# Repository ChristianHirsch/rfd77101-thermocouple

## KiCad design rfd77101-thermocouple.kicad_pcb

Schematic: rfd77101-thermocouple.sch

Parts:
C5: 1u; C_0603_1608Metric
C6: 10n; C_0603_1608Metric
C7: 100n; C_0603_1608Metric
D3: LED; LED_0603_1608Metric
J3: Conn_01x07; PinHeader_1x07_P2.54mm_Vertical
J4: Conn_01x02; TerminalBlock_RND_205-00241_1x02_P10.16mm_Horizontal
R4: R; R_0603_1608Metric
U1: RFD77101; RFDigital_RFD77101
U4: MAX31855KASA; SOIC-8_3.9x4.9mm_P1.27mm

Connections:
/BATT_V: U1.22; also elsewhere on the board
/BATT_V_EN: U1.12; also elsewhere on the board
/GPIO0: J3.6, U1.25
/GPIO1: J3.7, U1.23
/LED_1: D3.2, U1.11
/MISO: U1.27, U4.7
/SCK: U1.29, U4.5
/SWDCLK: J3.5, U1.9
/SWDIO/RESET: J3.4, U1.8
/~SS: U1.28, U4.6
GND: C5.2, C7.2, J3.1, R4.2, U1.1, U1.2, U1.4, U1.6, U1.19, U1.30, U1.42, U1.43, U1.44, U1.45, U4.1; also elsewhere on the board
unnamed: C6.1, J4.2, U4.3
unnamed: C6.2, J4.1, U4.2
unnamed: D3.1, R4.1
VBUS: J3.3; also elsewhere on the board
VDD: C5.1, C7.1, U1.7, U4.4; also elsewhere on the board

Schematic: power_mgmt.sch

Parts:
C1, C2: 4.7u; C_0603_1608Metric
C3, C4: 1u; C_0603_1608Metric
D1, D2: BAT20J; D_SOD-323
J1: USB_B_Micro; USB_Micro-B_Molex_47346-0001
J2: BATT_CONN; JST_PH_S2B-PH-K_1x02_P2.00mm_Horizontal
Q1: Q_NMOS_GSD; SOT-23
Q2, Q3: DMP3099L-13; SOT-23
R1: 3.1k; R_0603_1608Metric
R2: 8.2k; R_0603_1608Metric
R3, R5: 10k; R_0603_1608Metric
U2: MCP73811T-420I-OT; SOT-23-5
U3: TLV74130; SOT-23-5

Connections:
+BATT: C2.1, J2.1, Q2.3, Q3.2, R5.1, U2.3 (VBAT)
/BATT_V: R1.2, R2.1; also elsewhere on the board
/BATT_V_EN: Q1.1; also elsewhere on the board
GND: C1.2, C2.2, C3.2, C4.2, J1.5, J2.2, Q1.2, R2.2, R3.2, U2.2 (VSS), U3.2 (GND); also elsewhere on the board
unnamed: C1.1, D1.2, J1.1, U2.1 (CEN), U2.4 (VDD), U2.5 (PROG)
unnamed: C3.1, D2.1, Q2.2, U3.1 (VIN), U3.3 (EN)
unnamed: Q1.3, Q3.1, R5.2
unnamed: Q3.3, R1.1
VBUS: D1.1, D2.2, Q2.1, R3.1; also elsewhere on the board
VDD: C4.1, U3.5 (VOUT); also elsewhere on the board

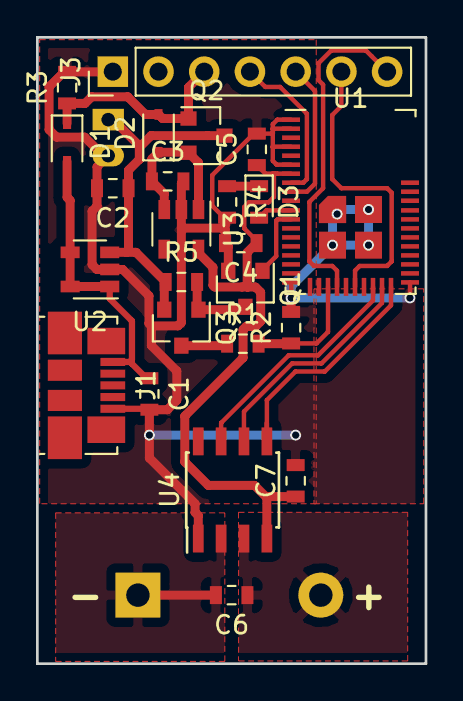
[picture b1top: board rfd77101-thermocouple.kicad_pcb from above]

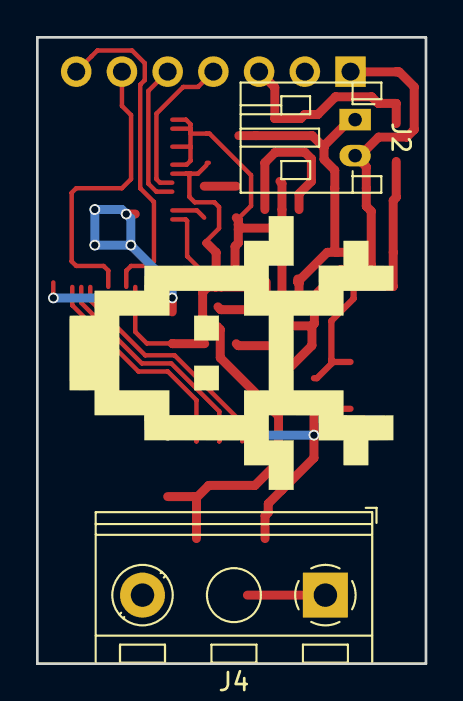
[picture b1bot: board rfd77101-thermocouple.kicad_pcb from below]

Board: 2 copper layers, 21.6 x 34.8 mm, 26 parts (2 on the bottom side), 21 nets.

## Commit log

2019-03-22 minors in PCB
